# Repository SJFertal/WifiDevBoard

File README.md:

STM32 based development board with 2.4Ghz communication capabilities

This board serves as my first experience with RF PCB design. This PCB has features such as: -Linear power regulation for low noise power supply -Proper impedance traces for RF and diff pair signal integrity -4 layers for consistent power plane coupling on signal layers 
-ESD protection for input signals 
-Proper antenna isolation 
-Signal layer ground pour and high stitching via count to reduce etching and improve coupling 
-Multiple GPIOs for application breadth 
MCU: STM32G47CB Transciever: NRF24L01P Regulator: LD1117

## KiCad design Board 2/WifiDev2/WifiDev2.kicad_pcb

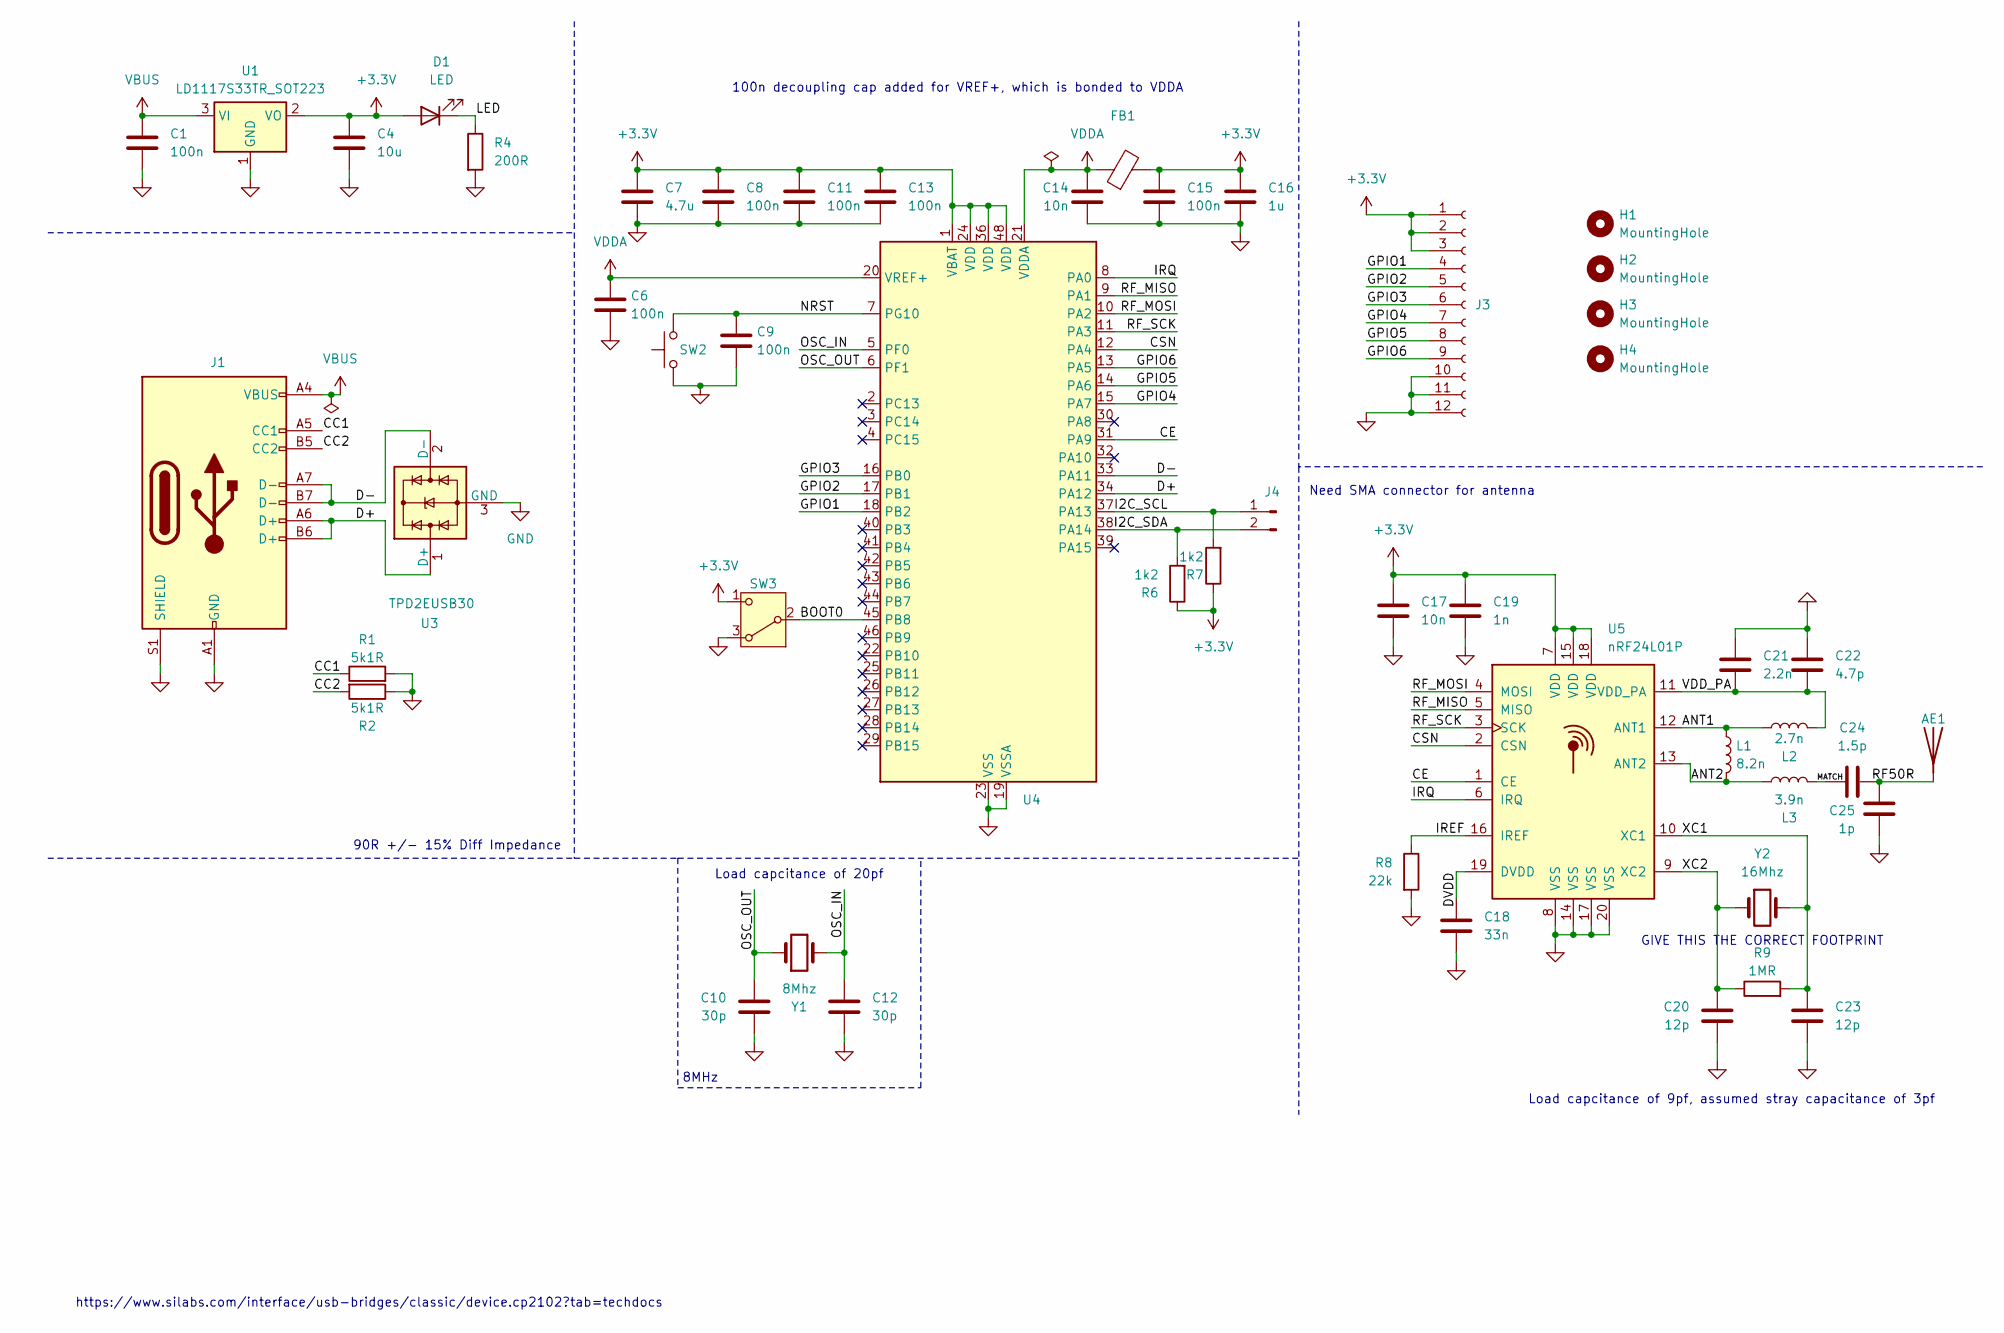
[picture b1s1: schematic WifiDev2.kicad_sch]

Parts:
AE1: Antenna; AMCA31-2R450G-S1F-T3
C1, C6, C8, C9, C11, C13, C15: 100n; C_0603_1608Metric
C4: 10u; C_0805_2012Metric
C7: 4.7u; C_0805_2012Metric
C10, C12: 30p; C_0603_1608Metric
C14, C17: 10n; C_0603_1608Metric
C16: 1u; C_0805_2012Metric
C18: 33n; C_0603_1608Metric
C19: 1n; C_0603_1608Metric
C20, C23: 12p; C_0603_1608Metric
C21: 2.2n; C_0603_1608Metric
C22: 4.7p; C_0603_1608Metric
C24: 1.5p; C_0603_1608Metric
C25: 1p; C_0603_1608Metric
D1: LED; LED_0603_1608Metric
FB1: FerriteBead; L_0603_1608Metric
H1, H2, H3, H4: MountingHole; MountingHole_2.2mm_M2_DIN965_Pad
J1: USB_C_Receptacle_USB2.0_14P; USB_C_Receptacle_G-Switch_GT-USB-7010ASV
J3: Conn_01x12_Socket; PinSocket_1x12_P2.54mm_Vertical
J4: Conn_01x02_Pin; PinHeader_1x02_P2.54mm_Vertical
L1: 8.2n; L_0603_1608Metric
L2: 2.7n; L_0603_1608Metric
L3: 3.9n; L_0603_1608Metric
R1, R2: 5k1R; R_0603_1608Metric
R4: 200R; R_0603_1608Metric
R6, R7: 1k2; R_0603_1608Metric
R8: 22k; R_0603_1608Metric
R9: 1MR; R_0805_2012Metric
SW2: SW_Push; SW_SPST_PTS647_Sx38
SW3: SW_Nidec_CAS-120A1; Nidec_Copal_CAS-120A
U1: LD1117S33TR_SOT223; SOT-223-3_TabPin2
U3: TPD2EUSB30; Texas_DRT-3
U4: STM32G4A1CETx; LQFP-48_7x7mm_P0.5mm
U5: nRF24L01P; QFN-20-1EP_4x4mm_P0.5mm_EP2.5x2.5mm
Y1: 8Mhz; Crystal_SMD_4Pin_3.2x2.5mm
Y2: 16Mhz; Crystal_SMD_4Pin_3.2x2.5mm

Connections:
+3.3V: C4.1, C7.1, C8.1, C11.1, C13.1, C15.1, C16.1, C17.1, C19.1, D1.2 (A), FB1.2, J3.1, J3.2, J3.3, R6.1, R7.1, SW3.1 (C), U1.2 (VO), U4.1 (VBAT), U4.24 (VDD), U4.36 (VDD), U4.48 (VDD), U5.7 (VDD), U5.15 (VDD), U5.18 (VDD)
/ANT1: L1.1, L2.2, U5.12 (ANT1)
/ANT2: L1.2, L3.2, U5.13 (ANT2)
/BOOT0: SW3.2 (B), U4.45 (PB8)
/CC1: J1.A5 (CC1), R1.1
/CC2: J1.B5 (CC2), R2.2
/CE: U4.31 (PA9), U5.1 (CE)
/CSN: U4.12 (PA4), U5.2 (CSN)
/D+: J1.A6 (D+), J1.B6 (D+), U3.1 (D+), U4.34 (PA12)
/D-: J1.A7 (D-), J1.B7 (D-), U3.2 (D-), U4.33 (PA11)
/DVDD: C18.1, U5.19 (DVDD)
/GPIO1: J3.4, U4.18 (PB2)
/GPIO2: J3.5, U4.17 (PB1)
/GPIO3: J3.6, U4.16 (PB0)
/GPIO4: J3.7, U4.15 (PA7)
/GPIO5: J3.8, U4.14 (PA6)
/GPIO6: J3.9, U4.13 (PA5)
/I2C_SCL: J4.1, R7.2, U4.37 (PA13)
/I2C_SDA: J4.2, R6.2, U4.38 (PA14)
/IREF: R8.1, U5.16 (IREF)
/IRQ: U4.8 (PA0), U5.6 (IRQ)
/LED: D1.1 (K), R4.1
/MATCH: C24.1, L3.1
/NRST: C9.1, SW2.2, U4.7 (PG10)
/OSC_IN: C12.1, U4.5 (PF0), Y1.2
/OSC_OUT: C10.1, U4.6 (PF1), Y1.1
/RF50R: AE1.1 (A), C24.2, C25.1
/RF_MISO: U4.9 (PA1), U5.5 (MISO)
/RF_MOSI: U4.10 (PA2), U5.4 (MOSI)
/RF_SCK: U4.11 (PA3), U5.3 (SCK)
/VDD_PA: C21.2, C22.2, L2.1, U5.11 (VDD_PA)
/XC1: C23.1, R9.2, U5.10 (XC1), Y2.2
/XC2: C20.1, R9.1, U5.9 (XC2), Y2.1
GND: C1.2, C4.2, C6.2, C7.2, C8.2, C9.2, C10.2, C11.2, C12.2, C13.2, C14.2, C15.2, C16.2, C17.2, C18.2, C19.2, C20.2, C21.1, C22.1, C23.2, C25.2, J1.A1 (GND), J1.A12 (GND), J1.B1 (GND), J1.B12 (GND), J1.S1 (SHIELD), J3.10, J3.11, J3.12, R1.2, R2.1, R4.2, R8.2, SW2.1, SW3.3 (A), U1.1 (GND), U3.3 (GND), U4.19 (VSSA), U4.23 (VSS), U4.35 (VSS), U4.47 (VSS), U5.8 (VSS), U5.14 (VSS), U5.17 (VSS), U5.20 (VSS)
VBUS: C1.1, J1.A4 (VBUS), J1.A9 (VBUS), J1.B4 (VBUS), J1.B9 (VBUS), U1.3 (VI)
VDDA: C6.1, C14.1, FB1.1, U4.20 (VREF+), U4.21 (VDDA)

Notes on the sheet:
https://www.silabs.com/interface/usb-bridges/classic/device.cp2102?tab=techdocs
GIVE THIS THE CORRECT FOOTPRINT
8MHz
Need SMA connector for antenna
90R +/- 15% Diff Impedance
Load capcitance of 9pf, assumed stray capacitance of 3pf
100n decoupling cap added for VREF+, which is bonded to VDDA
Load capcitance of 20pf

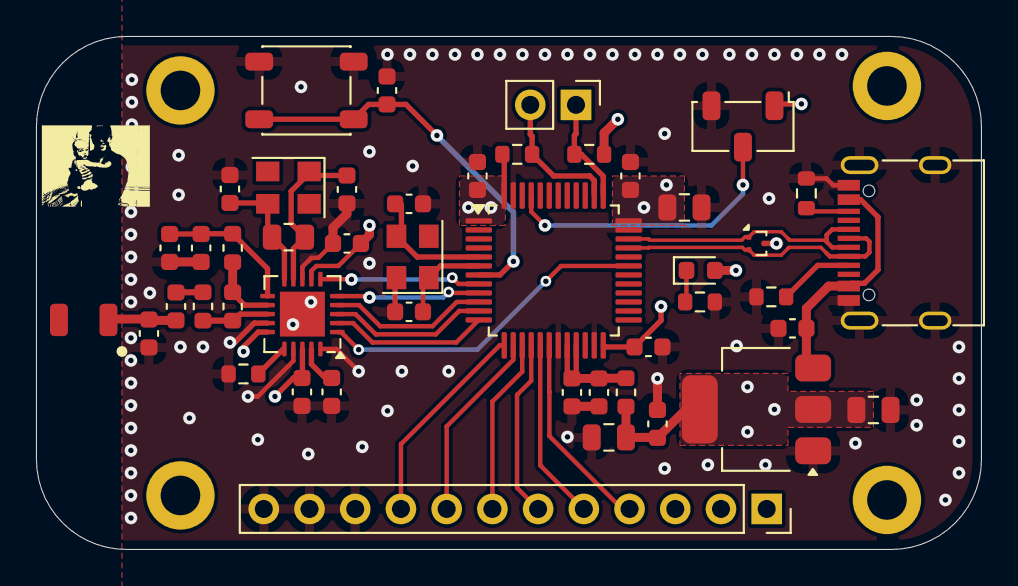
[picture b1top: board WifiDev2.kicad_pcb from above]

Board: 4 copper layers, 52.5 x 28.5 mm, 50 parts (0 on the bottom side), 36 nets.

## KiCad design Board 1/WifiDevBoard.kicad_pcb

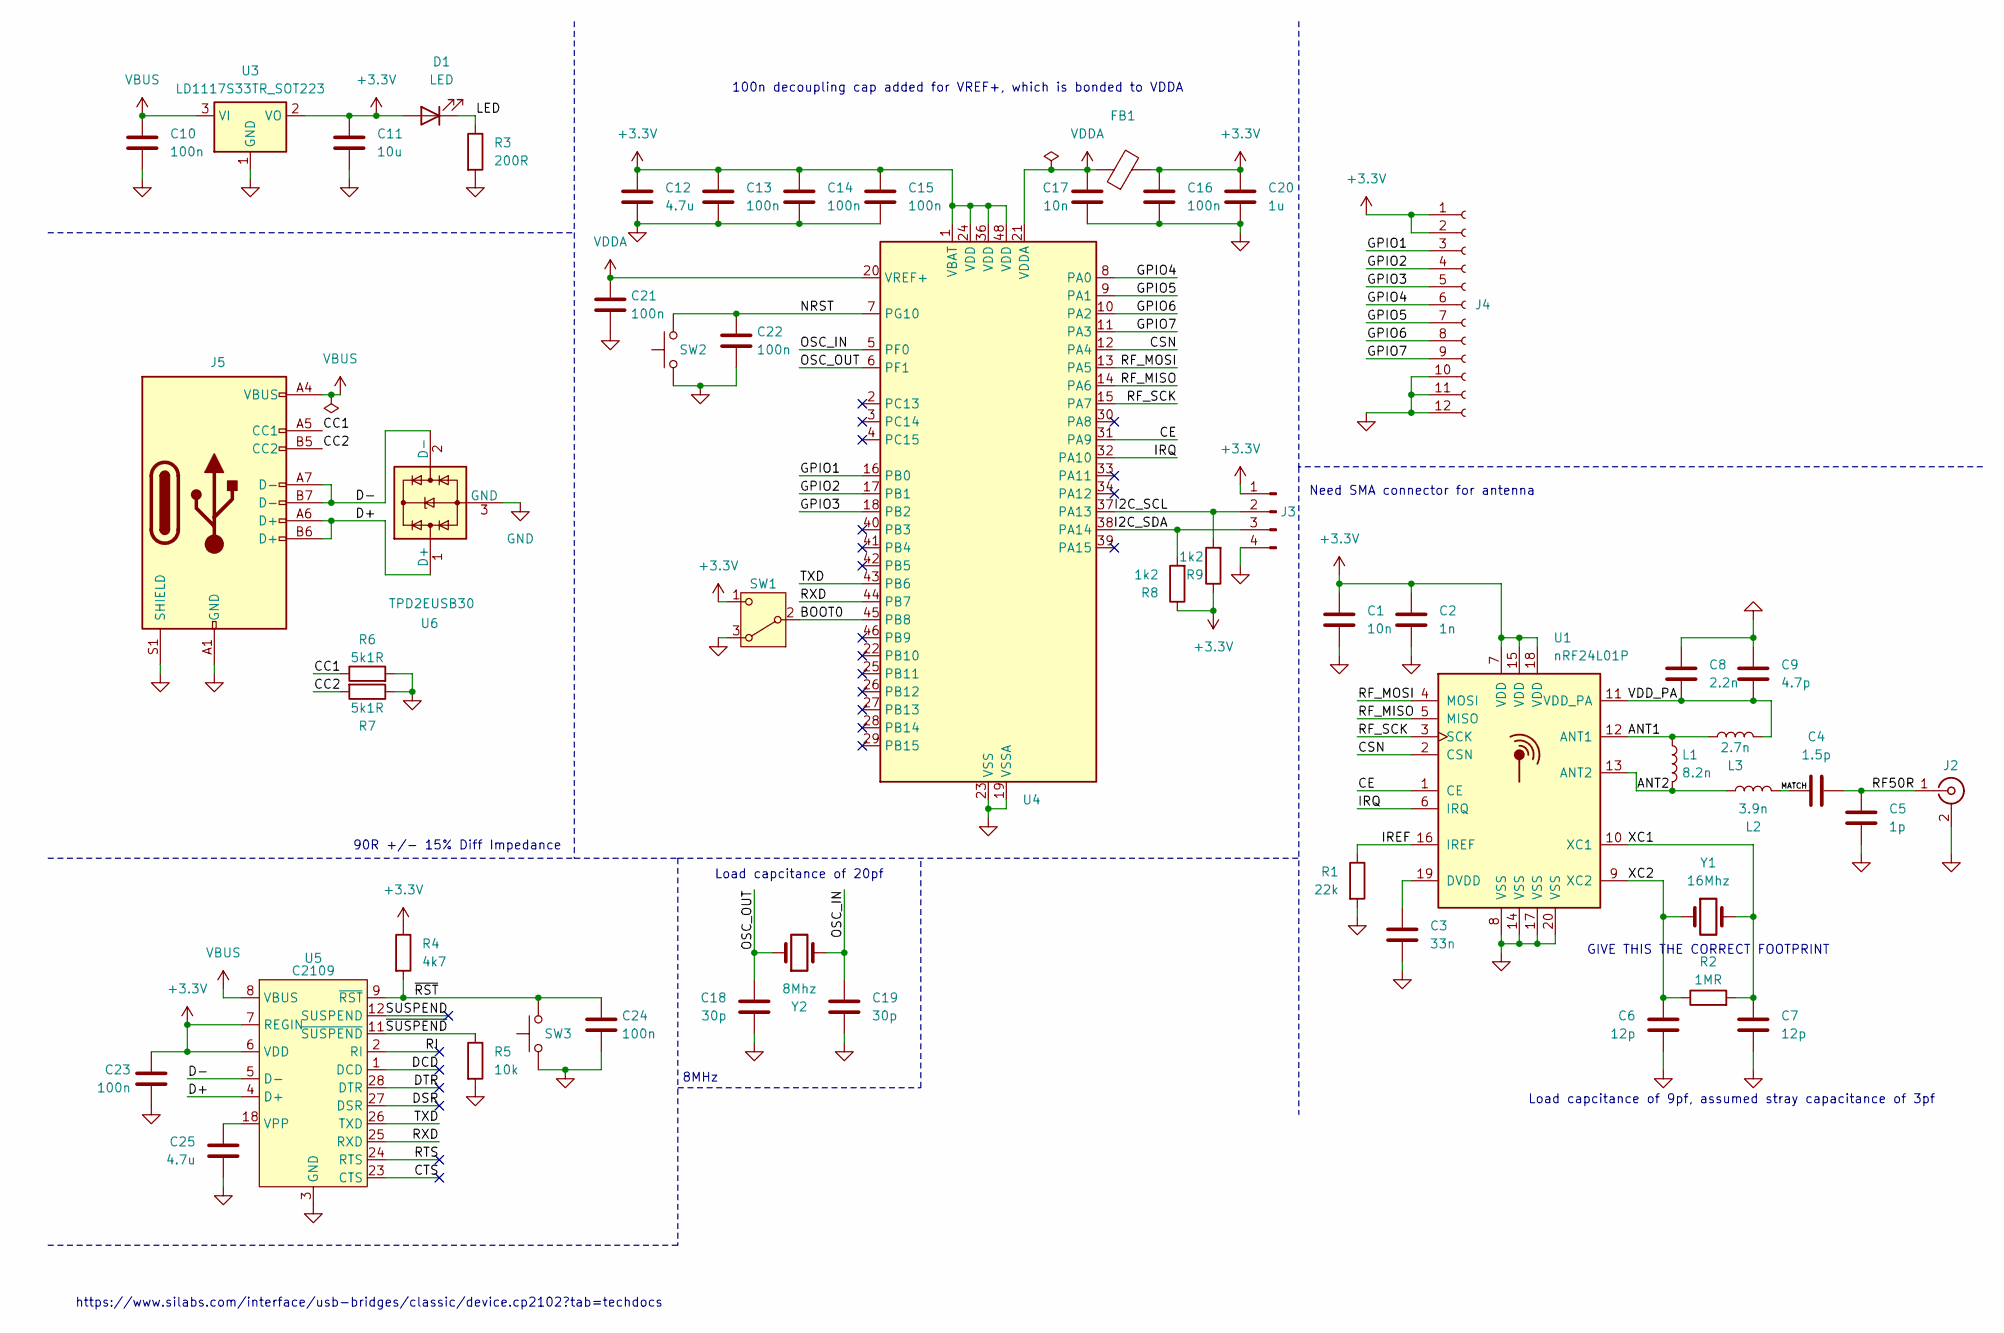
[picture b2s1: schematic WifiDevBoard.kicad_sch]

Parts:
C1, C17: 10n; C_0603_1608Metric
C2: 1n; C_0603_1608Metric
C3: 33n; C_0603_1608Metric
C4: 1.5p; C_0603_1608Metric
C5: 1p; C_0603_1608Metric
C6, C7: 12p; C_0603_1608Metric
C8: 2.2n; C_0603_1608Metric
C9: 4.7p; C_0603_1608Metric
C10, C13, C14, C15, C16, C21, C22, C23, C24: 100n; C_0603_1608Metric
C11: 10u; C_0805_2012Metric
C12, C25: 4.7u; C_0805_2012Metric
C18, C19: 30p; C_0603_1608Metric
C20: 1u; C_0805_2012Metric
D1: LED; LED_0603_1608Metric
FB1: FerriteBead; L_0603_1608Metric
J2: https://www.mouser.com/ProductDetail/GCT/RFPC-SMA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; SMA_Amphenol_901-144_Vertical
J3: Conn_01x04_Pin; JST_EH_B4B-EH-A_1x04_P2.50mm_Vertical
J4: Conn_01x12_Socket; PinSocket_1x12_P2.54mm_Vertical
J5: USB_C_Receptacle_USB2.0_14P; USB_C_Receptacle_G-Switch_GT-USB-7010ASV
L1: 8.2n; L_0603_1608Metric
L2: 3.9n; L_0603_1608Metric
L3: 2.7n; L_0603_1608Metric
R1: 22k; R_0805_2012Metric
R2: 1MR; R_0805_2012Metric
R3: 200R; R_0805_2012Metric
R4: 4k7; R_0805_2012Metric
R5: 10k; R_0805_2012Metric
R6, R7: 5k1R; R_0805_2012Metric
R8, R9: 1k2; R_0805_2012Metric
SW1: SW_Nidec_CAS-120A1; Nidec_Copal_CAS-120A
SW2, SW3: SW_Push; SW_SPST_PTS647_Sx38
U1: nRF24L01P; QFN-20-1EP_4x4mm_P0.5mm_EP2.5x2.5mm
U3: LD1117S33TR_SOT223; SOT-223-3_TabPin2
U4: STM32G4A1CETx; LQFP-48_7x7mm_P0.5mm
U5: C2109; QFN-28-1EP_5x5mm_P0.5mm_EP3.1x3.1mm
U6: TPD2EUSB30; Texas_DRT-3
Y1: 16Mhz; Crystal_SMD_4Pin_3.2x2.5mm
Y2: 8Mhz; Crystal_SMD_4Pin_3.2x2.5mm

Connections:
+3.3V: C1.1, C2.1, C11.1, C12.1, C13.1, C14.1, C15.1, C16.1, C20.1, C23.1, D1.2 (A), FB1.2, J3.1, J4.1, J4.2, R4.1, R8.1, R9.1, SW1.1 (C), U1.7 (VDD), U1.15 (VDD), U1.18 (VDD), U3.2 (VO), U4.1 (VBAT), U4.24 (VDD), U4.36 (VDD), U4.48 (VDD), U5.6 (VDD), U5.7 (REGIN)
/ANT1: L1.1, L3.2, U1.12 (ANT1)
/ANT2: L1.2, L2.2, U1.13 (ANT2)
/BOOT0: SW1.2 (B), U4.45 (PB8)
/CC1: J5.A5 (CC1), R6.1
/CC2: J5.B5 (CC2), R7.2
/CE: U1.1 (CE), U4.31 (PA9)
/CSN: U1.2 (CSN), U4.12 (PA4)
/CTS: U5.23 (CTS)
/D+: J5.A6 (D+), J5.B6 (D+), U5.4 (D+), U6.1 (D+)
/D-: J5.A7 (D-), J5.B7 (D-), U5.5 (D-), U6.2 (D-)
/DCD: U5.1 (DCD)
/DSR: U5.27 (DSR)
/DTR: U5.28 (DTR)
/GPIO1: J4.3, U4.16 (PB0)
/GPIO2: J4.4, U4.17 (PB1)
/GPIO3: J4.5, U4.18 (PB2)
/GPIO4: J4.6, U4.8 (PA0)
/GPIO5: J4.7, U4.9 (PA1)
/GPIO6: J4.8, U4.10 (PA2)
/GPIO7: J4.9, U4.11 (PA3)
/I2C_SCL: J3.2, R9.2, U4.37 (PA13)
/I2C_SDA: J3.3, R8.2, U4.38 (PA14)
/IREF: R1.1, U1.16 (IREF)
/IRQ: U1.6 (IRQ), U4.32 (PA10)
/LED: D1.1 (K), R3.1
/MATCH: C4.1, L2.1
/NRST: C22.1, SW2.2, U4.7 (PG10)
/OSC_IN: C19.1, U4.5 (PF0), Y2.2
/OSC_OUT: C18.1, U4.6 (PF1), Y2.1
/RF50R: C4.2, C5.1, J2.1 (In)
/RF_MISO: U1.5 (MISO), U4.14 (PA6)
/RF_MOSI: U1.4 (MOSI), U4.13 (PA5)
/RF_SCK: U1.3 (SCK), U4.15 (PA7)
/RI: U5.2 (RI)
/RTS: U5.24 (RTS)
/RXD: U4.44 (PB7), U5.25 (RXD)
/SUSPEND: U5.12 (SUSPEND)
/TXD: U4.43 (PB6), U5.26 (TXD)
/VDD_PA: C8.2, C9.2, L3.1, U1.11 (VDD_PA)
/XC1: C7.1, R2.2, U1.10 (XC1), Y1.2
/XC2: C6.1, R2.1, U1.9 (XC2), Y1.1
/~RST: C24.1, R4.2, SW3.2, U5.9 (~RST)
/~SUSPEND: R5.1, U5.11 (~SUSPEND)
GND: C1.2, C2.2, C3.2, C5.2, C6.2, C7.2, C8.1, C9.1, C10.2, C11.2, C12.2, C13.2, C14.2, C15.2, C16.2, C17.2, C18.2, C19.2, C20.2, C21.2, C22.2, C23.2, C24.2, C25.2, J2.2 (Ext), J3.4, J4.10, J4.11, J4.12, J5.A1 (GND), J5.A12 (GND), J5.B1 (GND), J5.B12 (GND), J5.S1 (SHIELD), R1.2, R3.2, R5.2, R6.2, R7.1, SW1.3 (A), SW2.1, SW3.1, U1.8 (VSS), U1.14 (VSS), U1.17 (VSS), U1.20 (VSS), U3.1 (GND), U4.19 (VSSA), U4.23 (VSS), U4.35 (VSS), U4.47 (VSS), U5.3 (GND), U6.3 (GND), Y1.3, Y1.4, Y2.3, Y2.4
unnamed: C3.1, U1.19 (DVDD)
unnamed: C25.1, U5.18 (VPP)
VBUS: C10.1, J5.A4 (VBUS), J5.A9 (VBUS), J5.B4 (VBUS), J5.B9 (VBUS), U3.3 (VI), U5.8 (VBUS)
VDDA: C17.1, C21.1, FB1.1, U4.20 (VREF+), U4.21 (VDDA)

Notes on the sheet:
100n decoupling cap added for VREF+, which is bonded to VDDA
GIVE THIS THE CORRECT FOOTPRINT
Load capcitance of 9pf, assumed stray capacitance of 3pf
Load capcitance of 20pf
90R +/- 15% Diff Impedance
8MHz
Need SMA connector for antenna
https://www.silabs.com/interface/usb-bridges/classic/device.cp2102?tab=techdocs

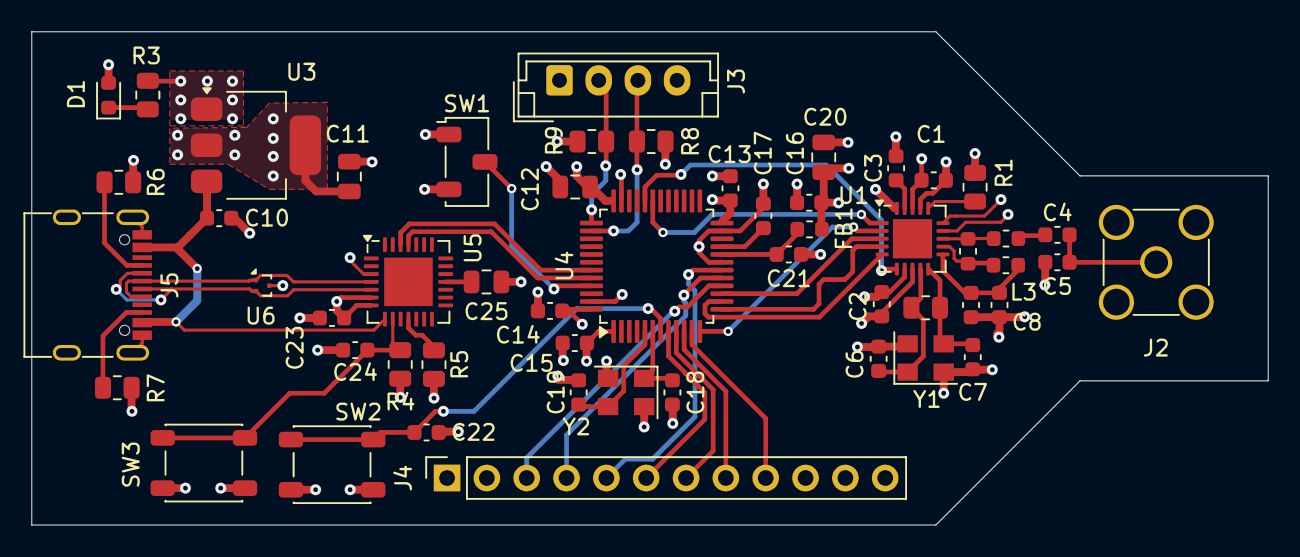
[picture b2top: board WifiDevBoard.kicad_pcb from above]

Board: 4 copper layers, 78.8 x 31.4 mm, 53 parts (0 on the bottom side), 42 nets.

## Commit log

2025-08-14 KiCAD Files
2025-08-20 First and Second boards, along with all datasheets
